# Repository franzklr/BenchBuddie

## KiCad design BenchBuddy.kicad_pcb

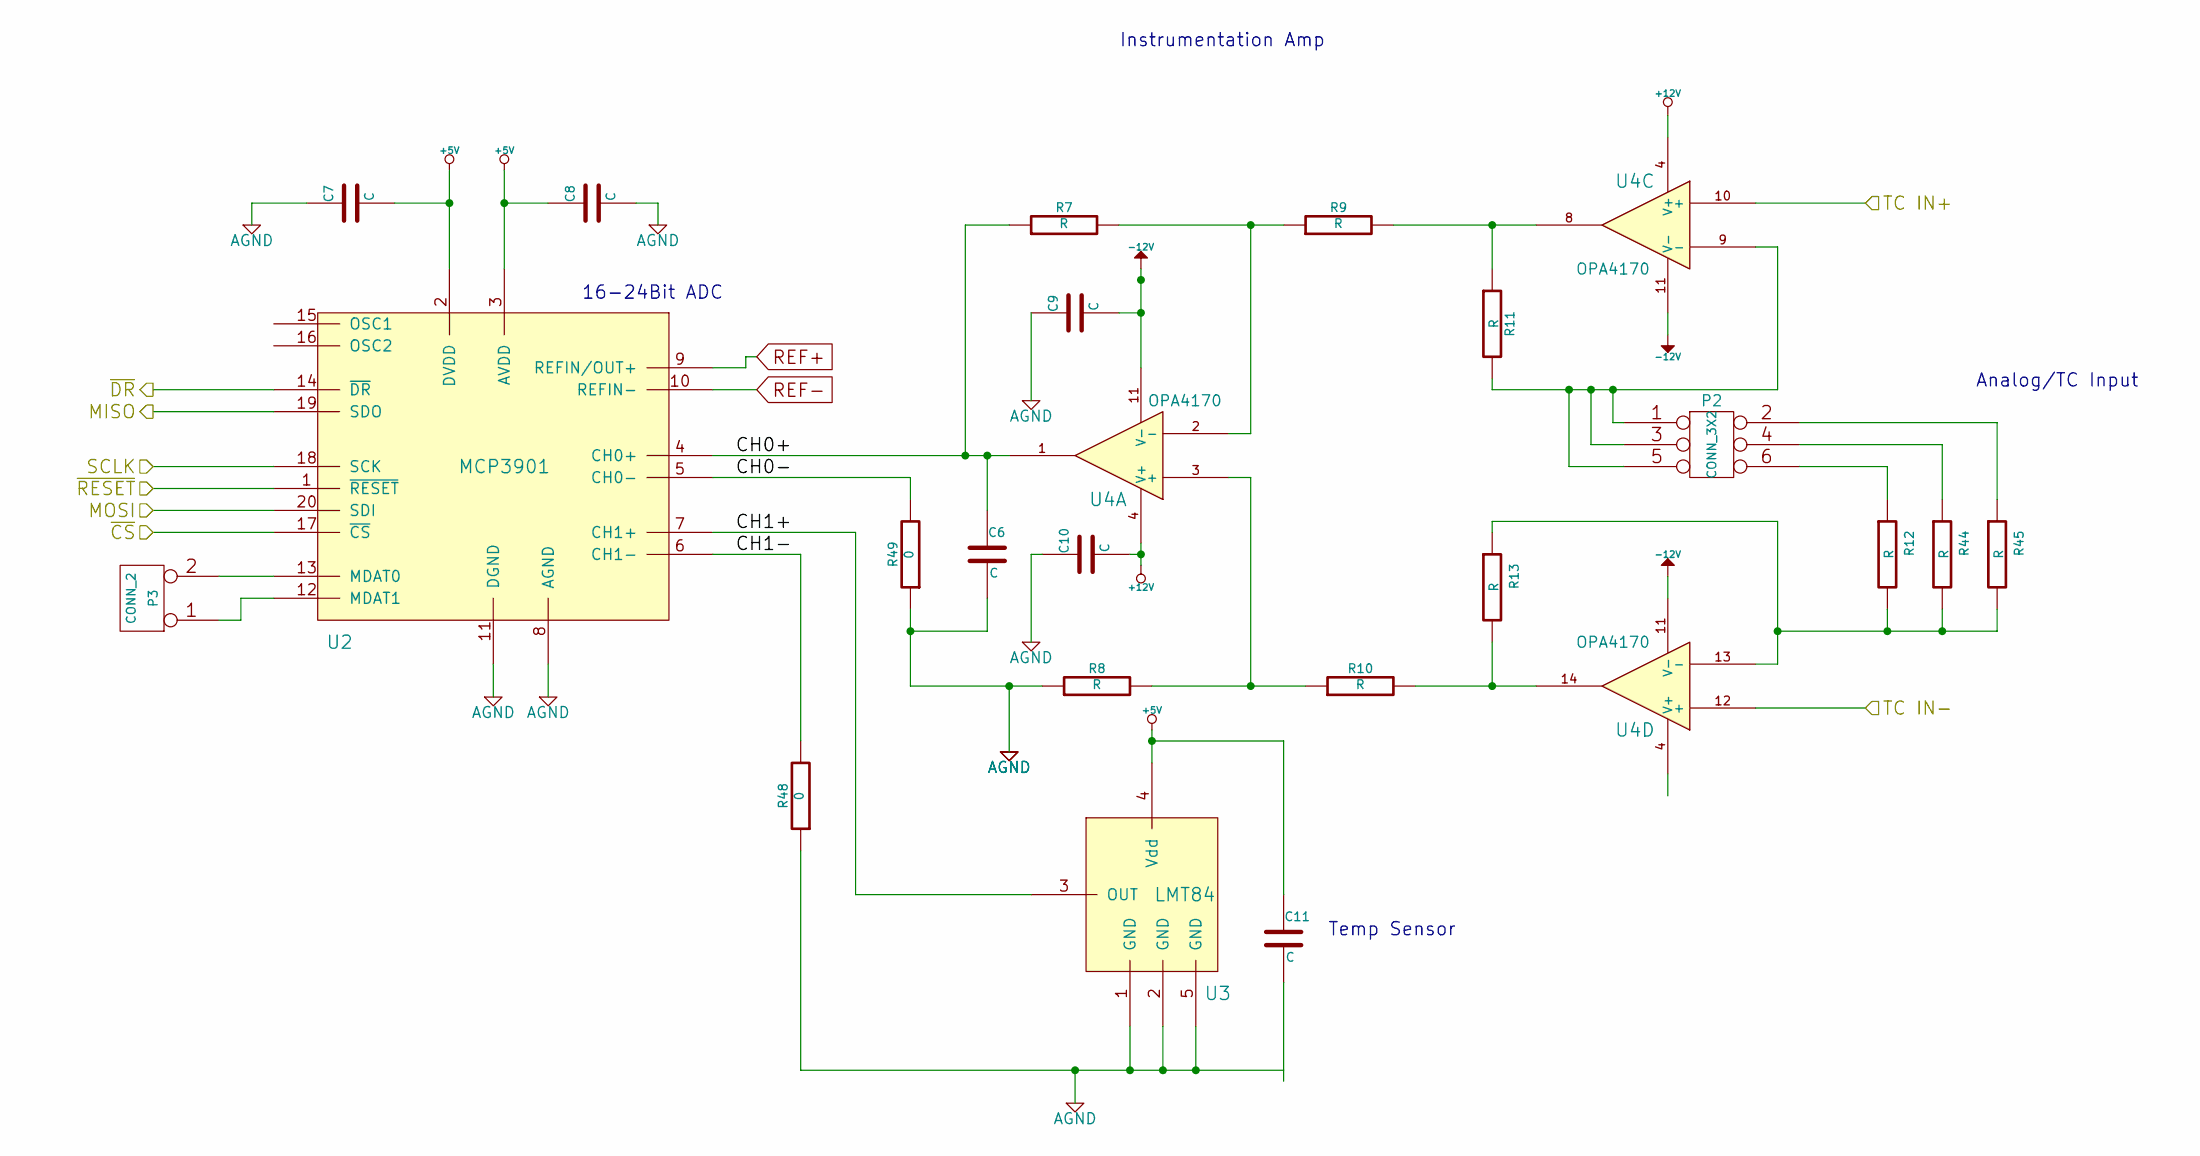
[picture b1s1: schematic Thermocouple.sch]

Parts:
C6, C7, C8, C9, C10, C11: C
P2: CONN_3X2
P3: CONN_2
R7, R8, R9, R10, R11, R12, R13, R44, R45: R
R48, R49: 0
U2: MCP3901
U3: LMT84
U4: OPA4170

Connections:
+5V: C7.2, C8.1, C11.1, U2.2 (DVDD), U2.3 (AVDD), U3.4 (Vdd); also elsewhere on the board
+12V: C10.2, U4.4 (V+); also elsewhere on the board
-12V: C9.2, U4.11 (V-); also elsewhere on the board
/Arduino/MISO: U2.19 (SDO); also elsewhere on the board
/Arduino/MOSI: U2.20 (SDI); also elsewhere on the board
/Arduino/SCLK: U2.18 (SCK); also elsewhere on the board
/Arduino/~ADC_CS: U2.17 (~CS); also elsewhere on the board
/Arduino/~DR: U2.14 (~DR); also elsewhere on the board
/Arduino/~RESET: U2.1 (~RESET); also elsewhere on the board
/Thermocouple/CH0+: C6.1, R7.1, U2.4 (CH0+), U4.1
/Thermocouple/CH0-: R49.2, U2.5 (CH0-)
/Thermocouple/CH1+: U2.7 (CH1+), U3.3 (OUT)
/Thermocouple/CH1-: R48.2, U2.6 (CH1-)
/Thermocouple/TC IN+: U4.10 (+); also elsewhere on the board
/Thermocouple/TC IN-: U4.12 (+); also elsewhere on the board
AGND: C6.2, C7.1, C8.2, C9.1, C10.1, R8.1, R48.1, R49.1, U2.8 (AGND), U2.11 (DGND), U3.1 (GND), U3.2 (GND), U3.5 (GND); also elsewhere on the board
unnamed: R12.2, R13.1, R44.2, R45.2, U4.13 (-)
unnamed: P2.2, R45.1
unnamed: P2.4, R44.1
unnamed: P3.2 (PM), U2.13 (MDAT0)
unnamed: P2.6, R12.1
unnamed: R8.2, R10.1, U4.3 (+)
unnamed: R9.2, R11.1, U4.8
unnamed: R10.2, R13.2, U4.14
unnamed: P2.1, P2.3, P2.5, R11.2, U4.9 (-)
unnamed: R7.2, R9.1, U4.2 (-)
unnamed: P3.1, U2.12 (MDAT1)

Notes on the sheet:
Instrumentation Amp
16-24Bit ADC
Analog/TC Input
Temp Sensor

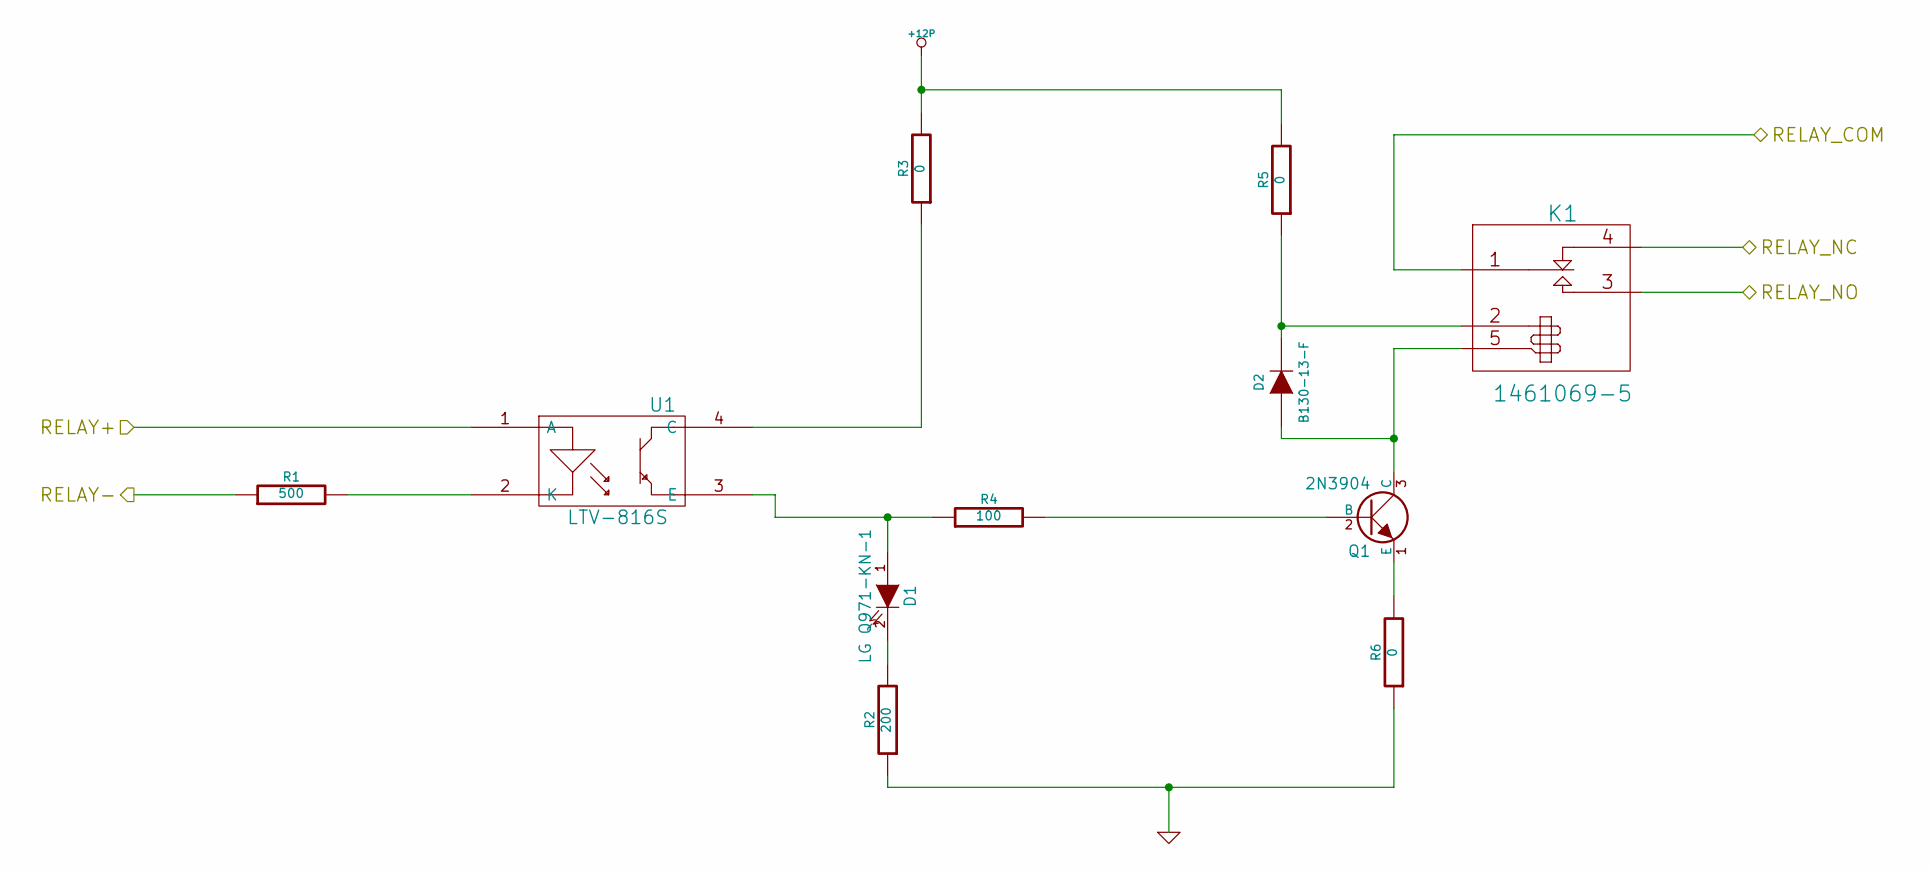
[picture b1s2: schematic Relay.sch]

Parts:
D1: LG Q971-KN-1
D2: B130-13-F
K1: 1461069-5
Q1: 2N3904; MFG Part Number MMBT3904-7-F
R1: 500
R2: 200
R3, R5, R6: 0
R4: 100
U1: LTV-816S; MFG Part Number LTV-816S

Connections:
+12P: R3.2, R5.2; also elsewhere on the board
/Arduino/RELAY+: U1.1 (A); also elsewhere on the board
/Arduino/RELAY-: R1.1; also elsewhere on the board
/Relay/RELAY_COM: K1.1 (COM); also elsewhere on the board
/Relay/RELAY_NC: K1.4 (NC); also elsewhere on the board
/Relay/RELAY_NO: K1.3 (NO); also elsewhere on the board
GND: R2.1, R6.1; also elsewhere on the board
unnamed: D1.2 (K), R2.2
unnamed: Q1.1 (E), R6.2
unnamed: R3.1, U1.4 (C)
unnamed: R1.2, U1.2 (K)
unnamed: Q1.2 (B), R4.2
unnamed: D2.2 (K), K1.2 (COIL+), R5.1
unnamed: D1.1 (A), R4.1, U1.3 (E)
unnamed: D2.1 (A), K1.5 (COIL-), Q1.3 (C)

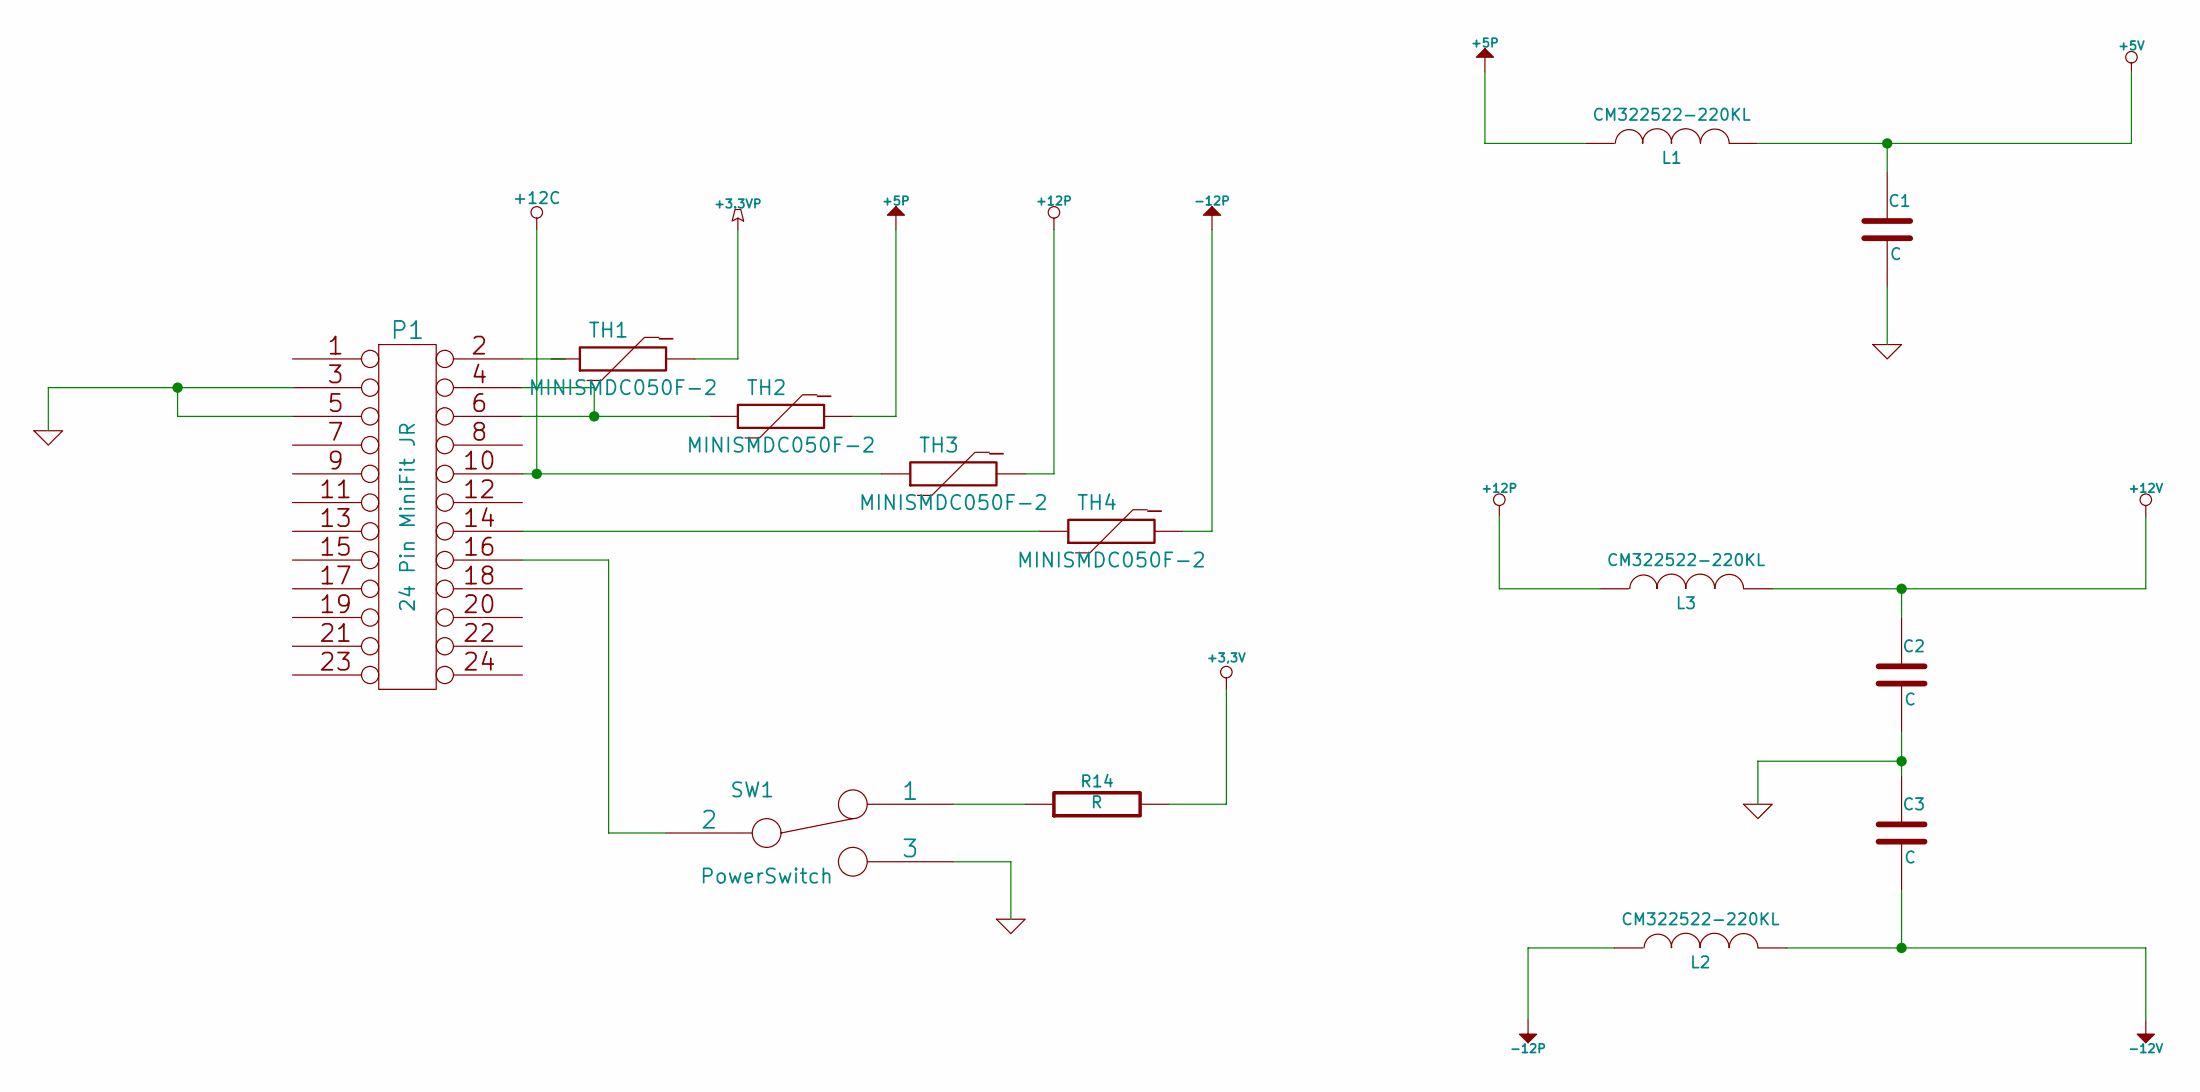
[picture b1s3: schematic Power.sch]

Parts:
C1, C2, C3: C
L1, L2, L3: CM322522-220KL
P1: 24 Pin MiniFit JR; MFG Part Number 39-30-1240
R14: R
SW1: PowerSwitch; MFG Part Number =s102011MA1QN1
TH1, TH2, TH3, TH4: MINISMDC050F-2; MFG Part Number MINISMDC050F-2

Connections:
+3.3V: R14.2; also elsewhere on the board
+5P: L1.1, TH2.2
+5V: C1.1, L1.2; also elsewhere on the board
+12C: P1.10, TH3.1; also elsewhere on the board
+12P: L3.1, TH3.2; also elsewhere on the board
+12V: C2.1, L3.2; also elsewhere on the board
-12P: L2.1, TH4.2
-12V: C3.2, L2.2; also elsewhere on the board
GND: C1.2, C2.2, C3.1, P1.3, P1.5, SW1.3; also elsewhere on the board
unnamed: P1.16, SW1.2
unnamed: R14.1, SW1.1
unnamed: P1.14, TH4.1
unnamed: P1.4, P1.6, TH2.1

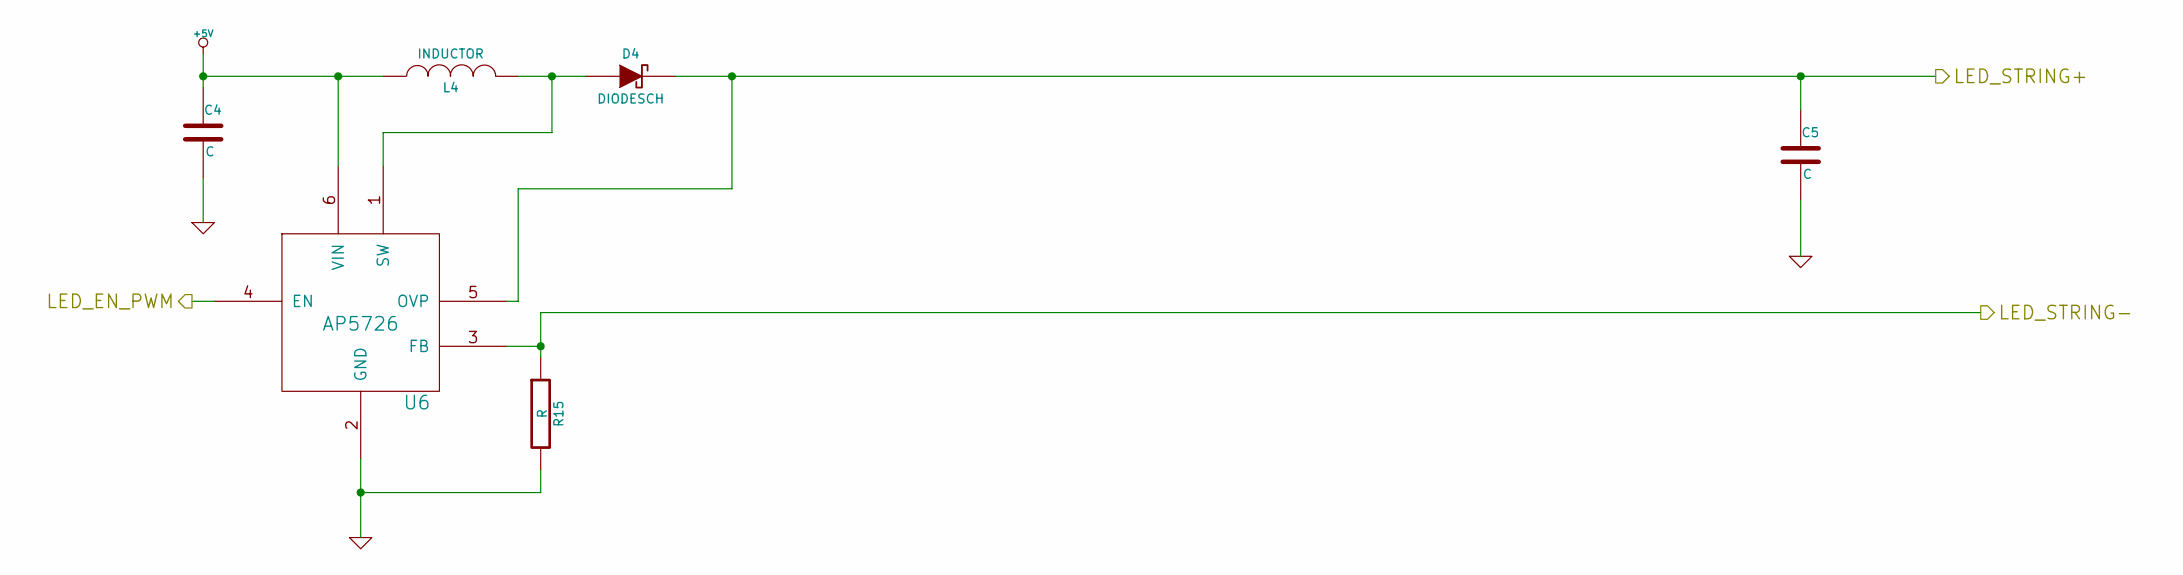
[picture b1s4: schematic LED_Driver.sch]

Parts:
C4, C5: C
D4: DIODESCH
L4: INDUCTOR
R15: R
U6: AP5726

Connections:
+5V: C4.1, L4.1, U6.6 (VIN); also elsewhere on the board
/Arduino/LED_EN_PWM: U6.4 (EN); also elsewhere on the board
/LED_Driver/LED_STRING+: C5.1, D4.2 (K), U6.5 (OVP); also elsewhere on the board
/LED_Driver/LED_STRING-: R15.1, U6.3 (FB); also elsewhere on the board
GND: C4.2, C5.2, R15.2, U6.2 (GND); also elsewhere on the board
unnamed: D4.1 (A), L4.2, U6.1 (SW)

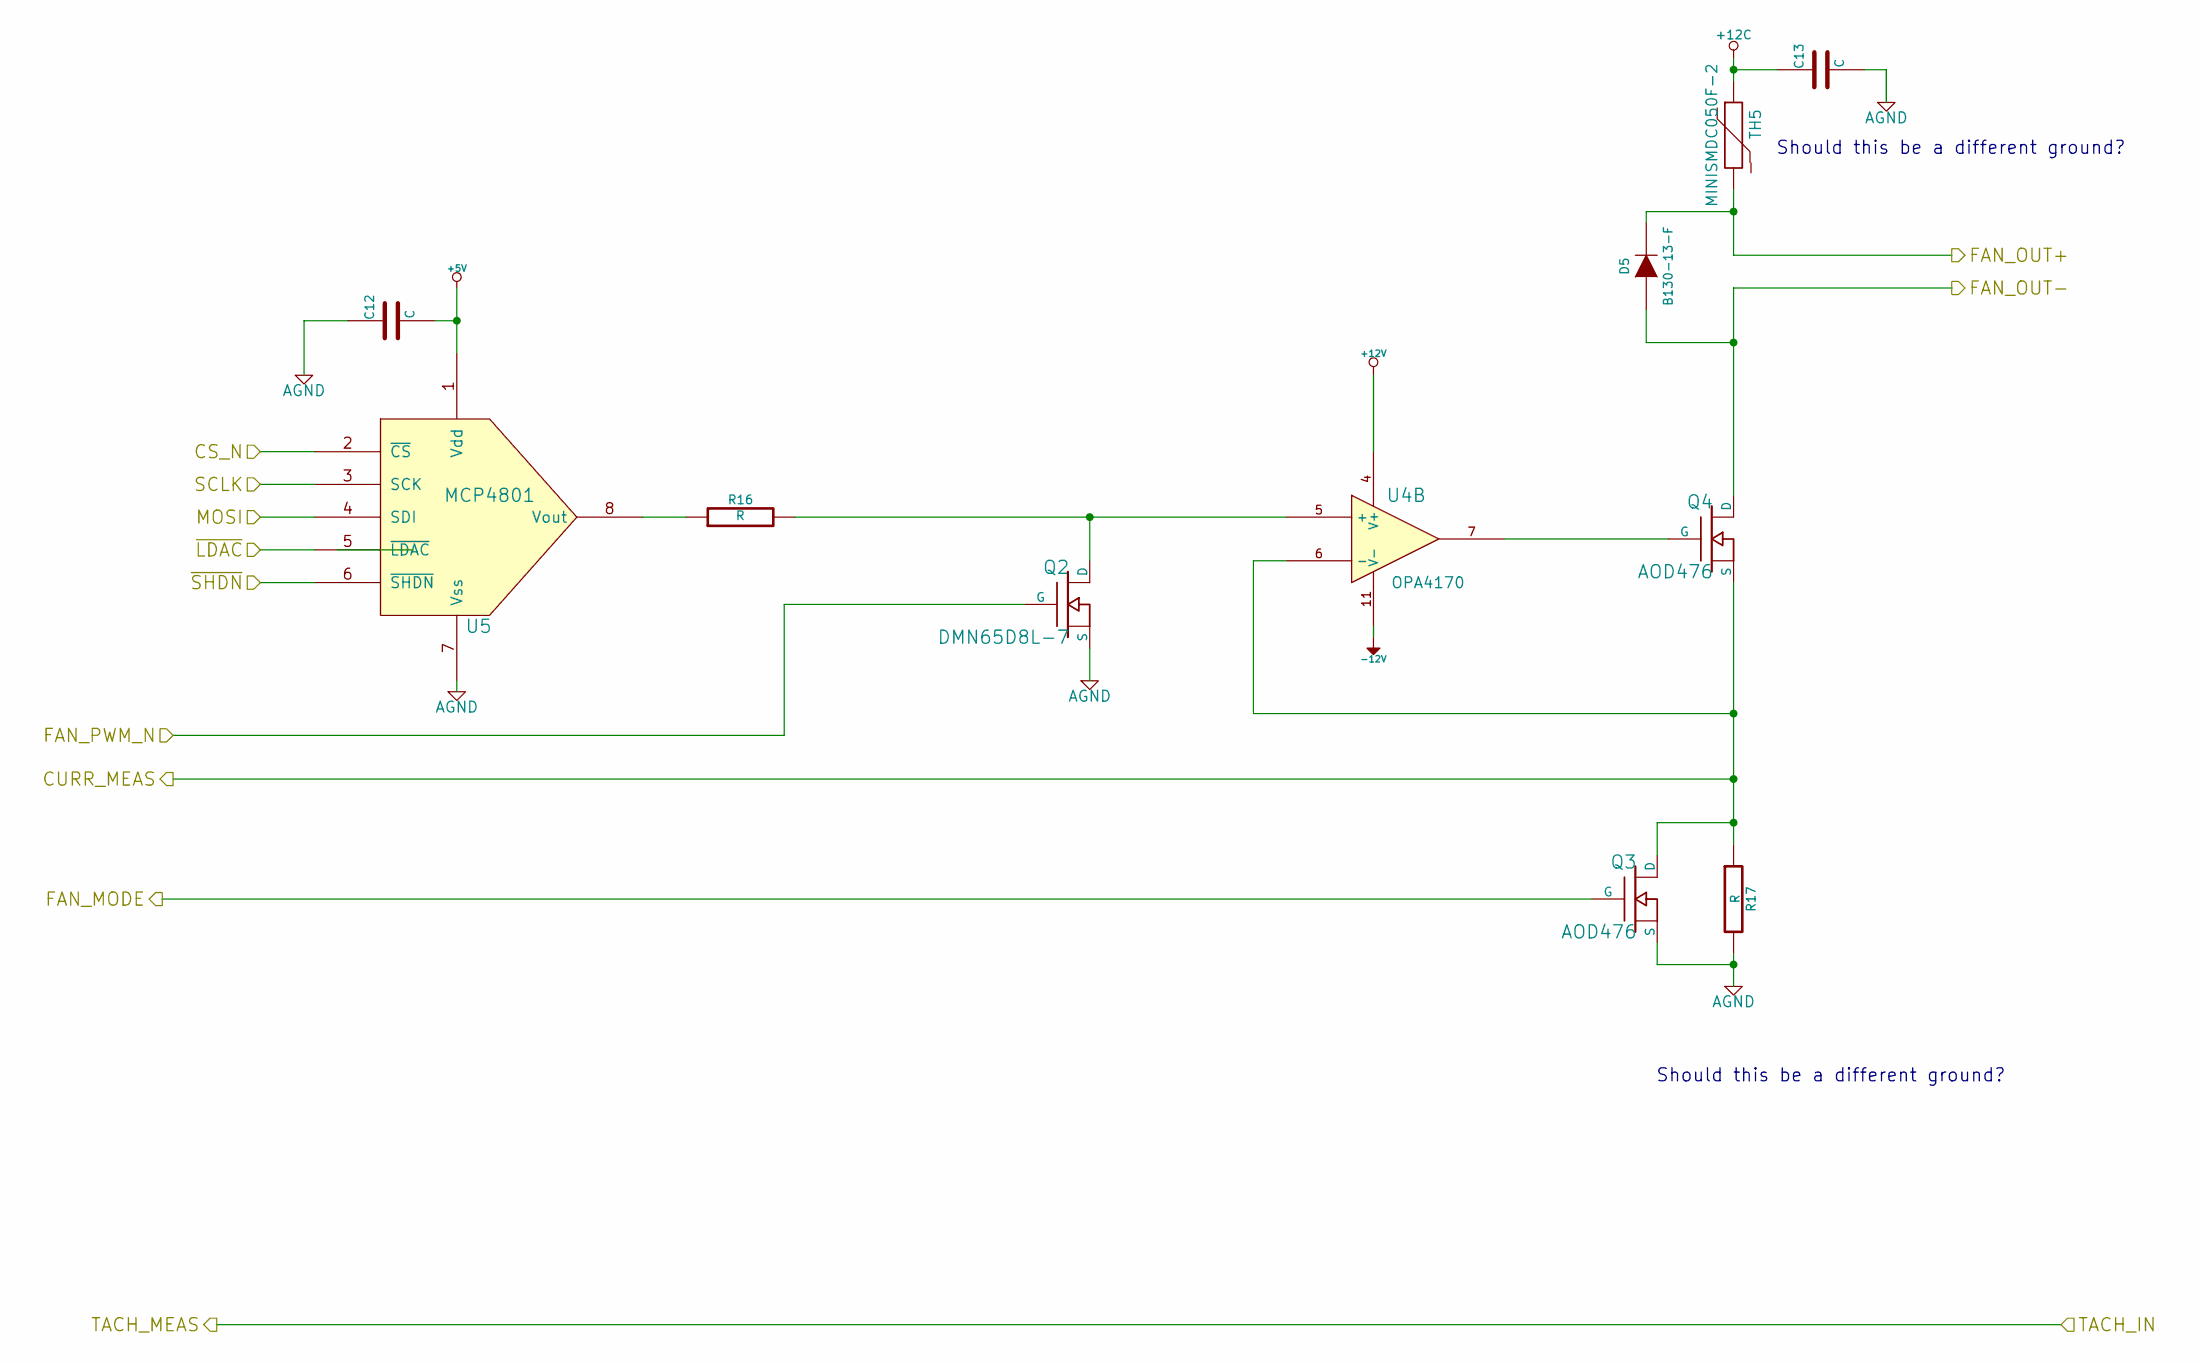
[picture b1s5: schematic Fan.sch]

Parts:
C12, C13: C
D5: B130-13-F; MFG Part Number B130-13-F
Q2: DMN65D8L-7; MFG Part Number DMN65D8L-7
Q3, Q4: AOD476; MFG Part Number AOD476
R16, R17: R
TH5: MINISMDC050F-2; MFG Part Number MINISMDC050F-2
U4: OPA4170
U5: MCP4801

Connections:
+5V: C12.2, U5.1 (Vdd); also elsewhere on the board
+12C: C13.1, TH5.1; also elsewhere on the board
+12V: U4.4 (V+); also elsewhere on the board
-12V: U4.11 (V-); also elsewhere on the board
/Arduino/CURR_MEAS: Q3.2 (D), Q4.3 (S), R17.1, U4.6 (-); also elsewhere on the board
/Arduino/FAN_MODE: Q3.1 (G); also elsewhere on the board
/Arduino/FAN_PWM: Q2.G; also elsewhere on the board
/Arduino/MOSI: U5.4 (SDI); also elsewhere on the board
/Arduino/SCLK: U5.3 (SCK); also elsewhere on the board
/Arduino/~LDAC: U5.5 (~LDAC); also elsewhere on the board
/Arduino/~SHDN: U5.6 (~SHDN); also elsewhere on the board
/Fan/CS_N: U5.2 (~CS); also elsewhere on the board
/Fan/FAN_OUT+: D5.2 (K), TH5.2; also elsewhere on the board
/Fan/FAN_OUT-: D5.1 (A), Q4.2 (D); also elsewhere on the board
AGND: C12.1, C13.2, Q2.3 (S), Q2.S, Q3.3 (S), R17.2, U5.7 (Vss); also elsewhere on the board
unnamed: R16.1, U5.8 (Vout)
unnamed: Q4.1 (G), U4.7
unnamed: Q2.2 (D), Q2.D, R16.2, U4.5 (+)

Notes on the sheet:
Should this be a different ground?

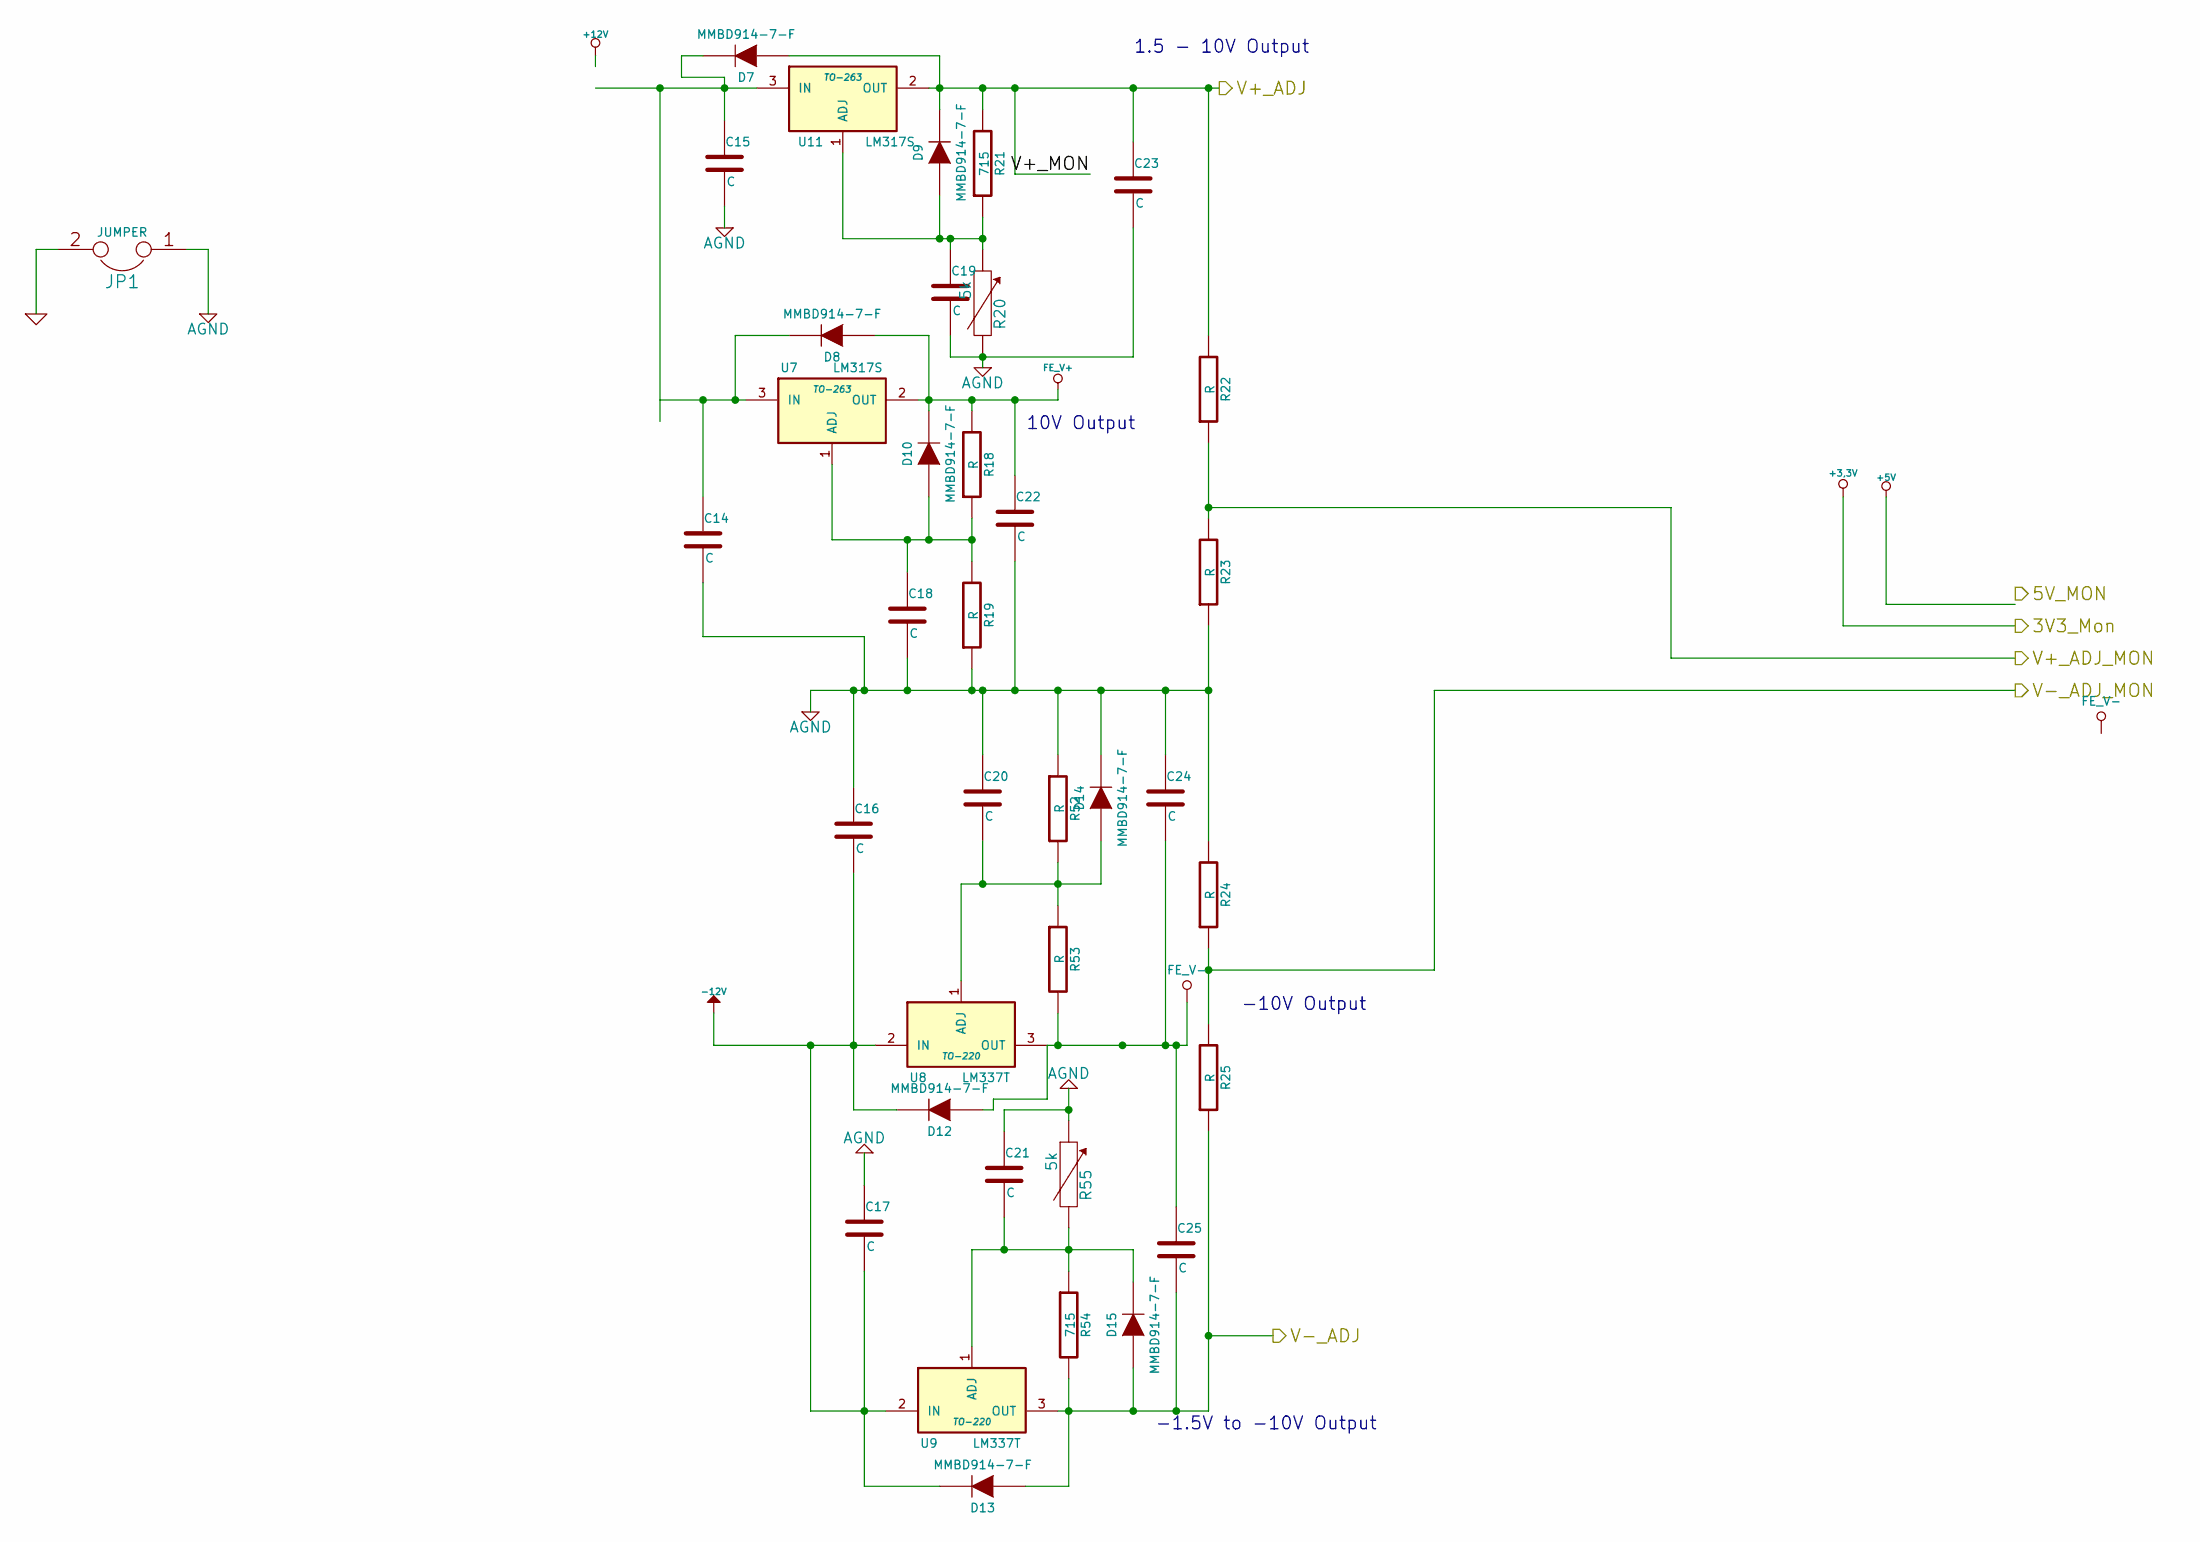
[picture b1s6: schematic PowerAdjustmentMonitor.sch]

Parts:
C14, C15, C16, C17, C18, C19, C20, C21, C22, C23, C24, C25: C
D7, D8, D9, D10, D12, D13, D14, D15: MMBD914-7-F
JP1: JUMPER
R18, R19, R22, R23, R24, R25, R52, R53: R
R20, R55: 5k
R21, R54: 715
U7, U11: LM317S; TO-263
U8, U9: LM337T; TO-220

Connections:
-12V: C16.2, C17.2, D12.2 (K), D13.2 (K), U8.2 (IN), U9.2 (IN); also elsewhere on the board
/Arduino/V+_ADJ_MON: R22.1, R23.2; also elsewhere on the board
/Arduino/V-_ADJ_MON: R24.1, R25.2; also elsewhere on the board
/PowerAdjustmentMonitor/V+_ADJ: C23.1, D7.1 (A), D9.2 (K), R21.2, R22.2, U11.2 (OUT); also elsewhere on the board
/PowerAdjustmentMonitor/V-_ADJ: C25.2, D13.1 (A), D15.1 (A), R25.1, R54.2, U9.3 (OUT); also elsewhere on the board
AGND: C14.2, C15.2, C16.1, C17.1, C18.2, C19.2, C20.1, C21.1, C22.2, C23.2, C24.1, D14.2 (K), JP1.1, R19.1, R20.2, R23.1, R24.2, R52.1, R55.1; also elsewhere on the board
FE_V+: C22.1, D8.1 (A), D10.2 (K), R18.2, U7.2 (OUT)
FE_V-: C24.2, C25.1, D12.1 (A), R53.2, U8.3 (OUT)
unnamed: C18.1, D10.1 (A), R18.1, R19.2, U7.1 (ADJ)
unnamed: C14.1, D8.2 (K), U7.3 (IN)
unnamed: C21.2, D15.2 (K), R54.1, R55.2, U9.1 (ADJ)
unnamed: C20.2, D14.1 (A), R52.2, R53.1, U8.1 (ADJ)
unnamed: C15.1, D7.2 (K), U11.3 (IN)
unnamed: C19.1, D9.1 (A), R20.1, R21.1, U11.1 (ADJ)

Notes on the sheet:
10V Output
1.5 - 10V Output
-1.5V to -10V Output
-10V Output

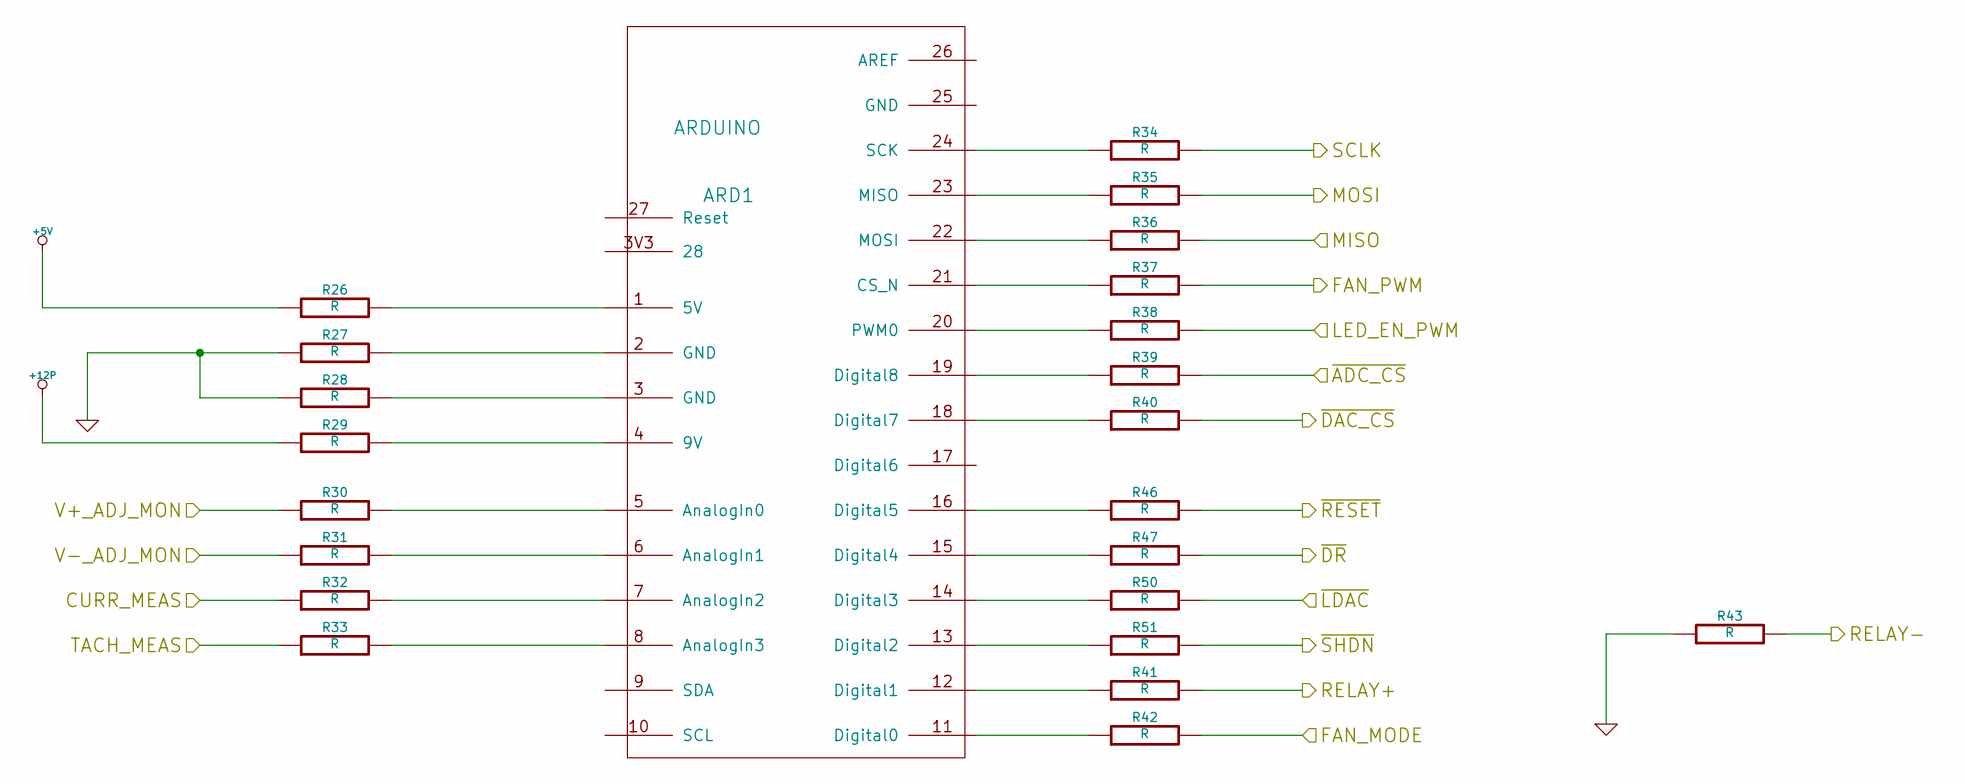
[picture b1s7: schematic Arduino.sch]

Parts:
ARD1: ARDUINO
R26, R27, R28, R29, R30, R31, R32, R33, R34, R35, R36, R37, R38, R39, R40, R41, R42, R43, R46, R47, R50, R51: R

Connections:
+5V: R26.1; also elsewhere on the board
+12P: R29.1; also elsewhere on the board
/Arduino/CURR_MEAS: R32.1; also elsewhere on the board
/Arduino/FAN_MODE: R42.2; also elsewhere on the board
/Arduino/FAN_PWM: R37.2; also elsewhere on the board
/Arduino/LED_EN_PWM: R38.2; also elsewhere on the board
/Arduino/MISO: R36.2; also elsewhere on the board
/Arduino/MOSI: R35.2; also elsewhere on the board
/Arduino/RELAY+: R41.2; also elsewhere on the board
/Arduino/RELAY-: R43.2; also elsewhere on the board
/Arduino/SCLK: R34.2; also elsewhere on the board
/Arduino/V+_ADJ_MON: R30.1; also elsewhere on the board
/Arduino/V-_ADJ_MON: R31.1; also elsewhere on the board
/Arduino/~ADC_CS: R39.2; also elsewhere on the board
/Arduino/~DR: R47.2; also elsewhere on the board
/Arduino/~LDAC: R50.2; also elsewhere on the board
/Arduino/~RESET: R46.2; also elsewhere on the board
/Arduino/~SHDN: R51.2; also elsewhere on the board
/Fan/CS_N: R40.2; also elsewhere on the board
/Fan/TACH_IN: R33.1; also elsewhere on the board
GND: R27.1, R28.1, R43.1; also elsewhere on the board
unnamed: ARD1.20 (PWM0), R38.1
unnamed: ARD1.22 (MOSI), R36.1
unnamed: ARD1.23 (MISO), R35.1
unnamed: ARD1.24 (SCK), R34.1
unnamed: ARD1.6 (AnalogIn1), R31.2
unnamed: ARD1.5 (AnalogIn0), R30.2
unnamed: ARD1.12 (Digital1), R41.1
unnamed: ARD1.11 (Digital0), R42.1
unnamed: ARD1.21 (CS_N), R37.1
unnamed: ARD1.18 (Digital7), R40.1
unnamed: ARD1.19 (Digital8), R39.1
unnamed: ARD1.7 (AnalogIn2), R32.2
unnamed: ARD1.8 (AnalogIn3), R33.2
unnamed: ARD1.13 (Digital2), R51.1
unnamed: ARD1.15 (Digital4), R47.1
unnamed: ARD1.4 (9V), R29.2
unnamed: ARD1.3 (GND), R28.2
unnamed: ARD1.2 (GND), R27.2
unnamed: ARD1.14 (Digital3), R50.1
unnamed: ARD1.1 (5V), R26.2
unnamed: ARD1.16 (Digital5), R46.1

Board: 4 copper layers, 123 parts (36 on the bottom side), 99 nets, no tracks yet.

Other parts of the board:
P4: 12 Pin Terminal Block; 12PinTB
P5: 3 Pin TB; 3PinTB

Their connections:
+3.3V: P4.1; also elsewhere on the board
+5V: P4.2; also elsewhere on the board
/Fan/FAN_OUT+: P4.8; also elsewhere on the board
/Fan/FAN_OUT-: P4.9; also elsewhere on the board
/Fan/TACH_IN: P4.10; also elsewhere on the board
/LED_Driver/LED_STRING+: P4.6; also elsewhere on the board
/LED_Driver/LED_STRING-: P4.7; also elsewhere on the board
/PowerAdjustmentMonitor/V+_ADJ: P4.4; also elsewhere on the board
/PowerAdjustmentMonitor/V-_ADJ: P4.5; also elsewhere on the board
/Relay/RELAY_COM: P5.2; also elsewhere on the board
/Relay/RELAY_NC: P5.3; also elsewhere on the board
/Relay/RELAY_NO: P5.1; also elsewhere on the board
/Thermocouple/TC IN+: P4.11; also elsewhere on the board
/Thermocouple/TC IN-: P4.12; also elsewhere on the board
GND: P4.3; also elsewhere on the board

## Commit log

2014-01-31 Erste Kicad Dateien
2014-01-31 Erste grobe Struktur
2014-02-04 Added Powercontrol stuff
2014-02-06 Struktur nach Arduino
2014-02-07 Fan/Current Module Refactoring
2014-02-15 Am Ende der 4. Woche
2014-02-18 Nach Einfuegen Relay-Modul
2014-02-23 Am Ende der 5. Woche.
